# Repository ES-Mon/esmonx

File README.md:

# esmonx
Electro static field monitor

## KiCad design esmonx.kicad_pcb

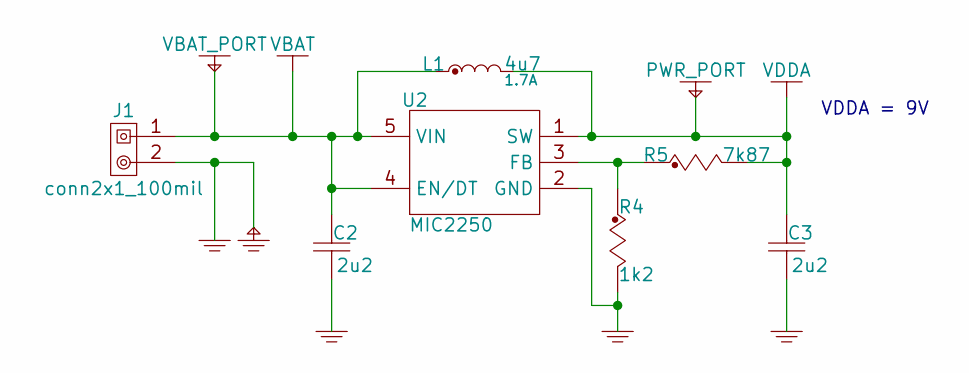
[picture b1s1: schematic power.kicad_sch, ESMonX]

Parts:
C2, C3: 2u2; C_0603_1608Metric; Voltage 25V; MFG PN CL10A225KP8NNNC
J1: conn2x1_100mil; PinHeader_1x02_P2.54mm_Vertical
L1: 4u7; NRS4018T4R7MDGJ; MFG PN LSXND4040TKL4R7MDG
R4: 1k2; R_0603_1608Metric; Tolerance 1%; MFG PN CR0603-FX-1201ELF
R5: 7k87; R_0603_1608Metric; Tolerance 1%; MFG PN CR0603-FX-7871ELF
U2: MIC2250; SOT-23-5; MFG PN MIC2250-1YD5-TR

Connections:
GND: C2.1, C3.1, J1.2, R4.2, U2.2 (GND); also elsewhere on the board
unnamed: R4.1, R5.1, U2.3 (FB)
VBAT: C2.2, J1.1, L1.1, U2.4 (EN/DT), U2.5 (VIN); also elsewhere on the board
VDDA: C3.2, L1.2, R5.2, U2.1 (SW); also elsewhere on the board

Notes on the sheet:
VDDA = 9V

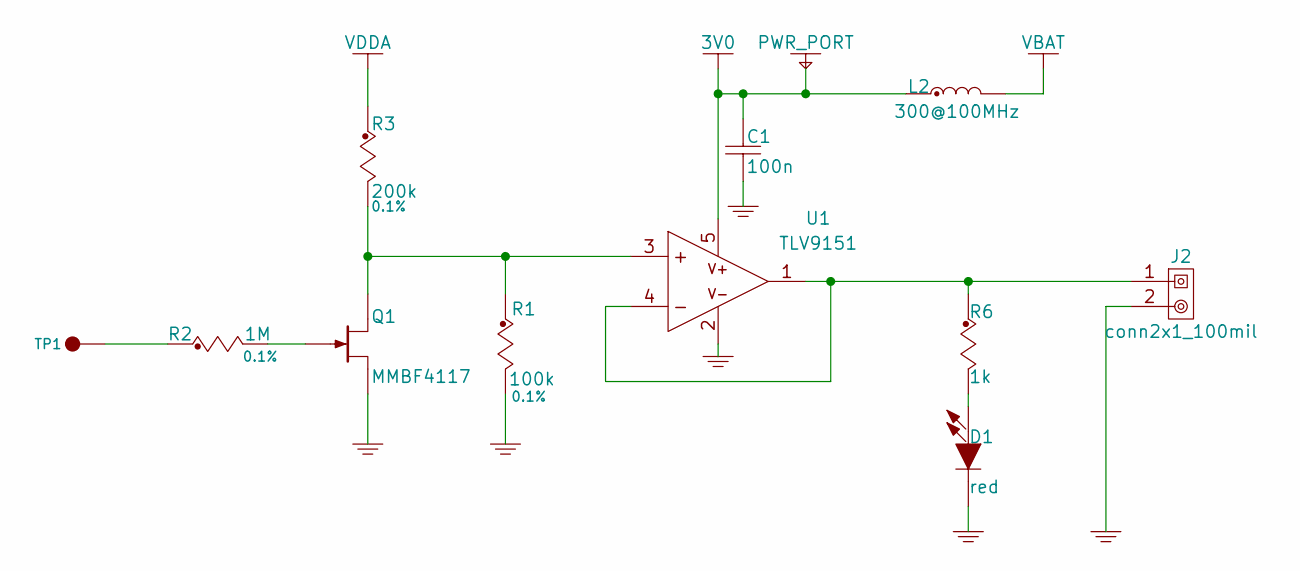
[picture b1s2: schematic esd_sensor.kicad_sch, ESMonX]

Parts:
C1: 100n; C_0603_1608Metric; Voltage 50V; MFG PN CL10B104JB8NNNC
D1: red; LED_0603_1608Metric; MFG PN 150060RS55040
J2: conn2x1_100mil; PinHeader_1x02_P2.54mm_Vertical
L2: 300@100MHz; L_0603_1608Metric; MFG PN PBY160808T-301Y-N
Q1: MMBF4117; SOT-23-3; MFG PN MMBF4117
R1: 100k; R_0603_1608Metric; Tolerance 0.1%; MFG PN ERA-3VEB1003V
R2: 1M; R_0603_1608Metric; Tolerance 0.1%; MFG PN RT0603BRD071ML
R3: 200k; R_0603_1608Metric; Tolerance 0.1%; MFG PN RE0603BRE07200KL
R6: 1k; R_0603_1608Metric; Tolerance 1%; MFG PN CR0603-FX-1001ELF
TP1: tp_smt; TestPoint_Pad_D1.0mm
U1: TLV9151; SOT-23-5; MFG PN TLV9151SIDBVR

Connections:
3V0: C1.2, L2.1, U1.5 (V+)
GND: C1.1, D1.1 (K), J2.2, Q1.1 (S), R1.2, U1.2 (V-); also elsewhere on the board
unnamed: D1.2 (A), R6.2
unnamed: Q1.2 (D), R1.1, R3.2, U1.3 (INA+)
unnamed: Q1.3 (G), R2.2
unnamed: R2.1, TP1.1
unnamed: J2.1, R6.1, U1.1 (OUTA), U1.4 (INA-)
VBAT: L2.2; also elsewhere on the board
VDDA: R3.1; also elsewhere on the board

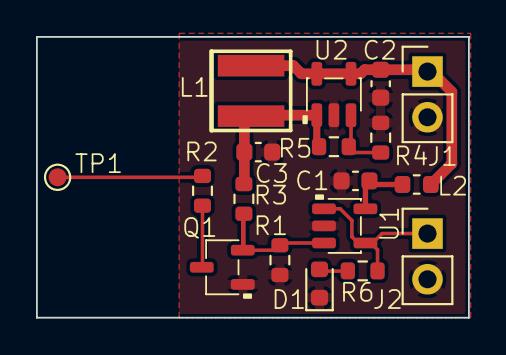
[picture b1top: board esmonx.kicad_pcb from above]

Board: 2 copper layers, 24.0 x 15.6 mm, 18 parts (0 on the bottom side), 10 nets.

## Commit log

2025-10-07 U1 mfg partnumber updated
